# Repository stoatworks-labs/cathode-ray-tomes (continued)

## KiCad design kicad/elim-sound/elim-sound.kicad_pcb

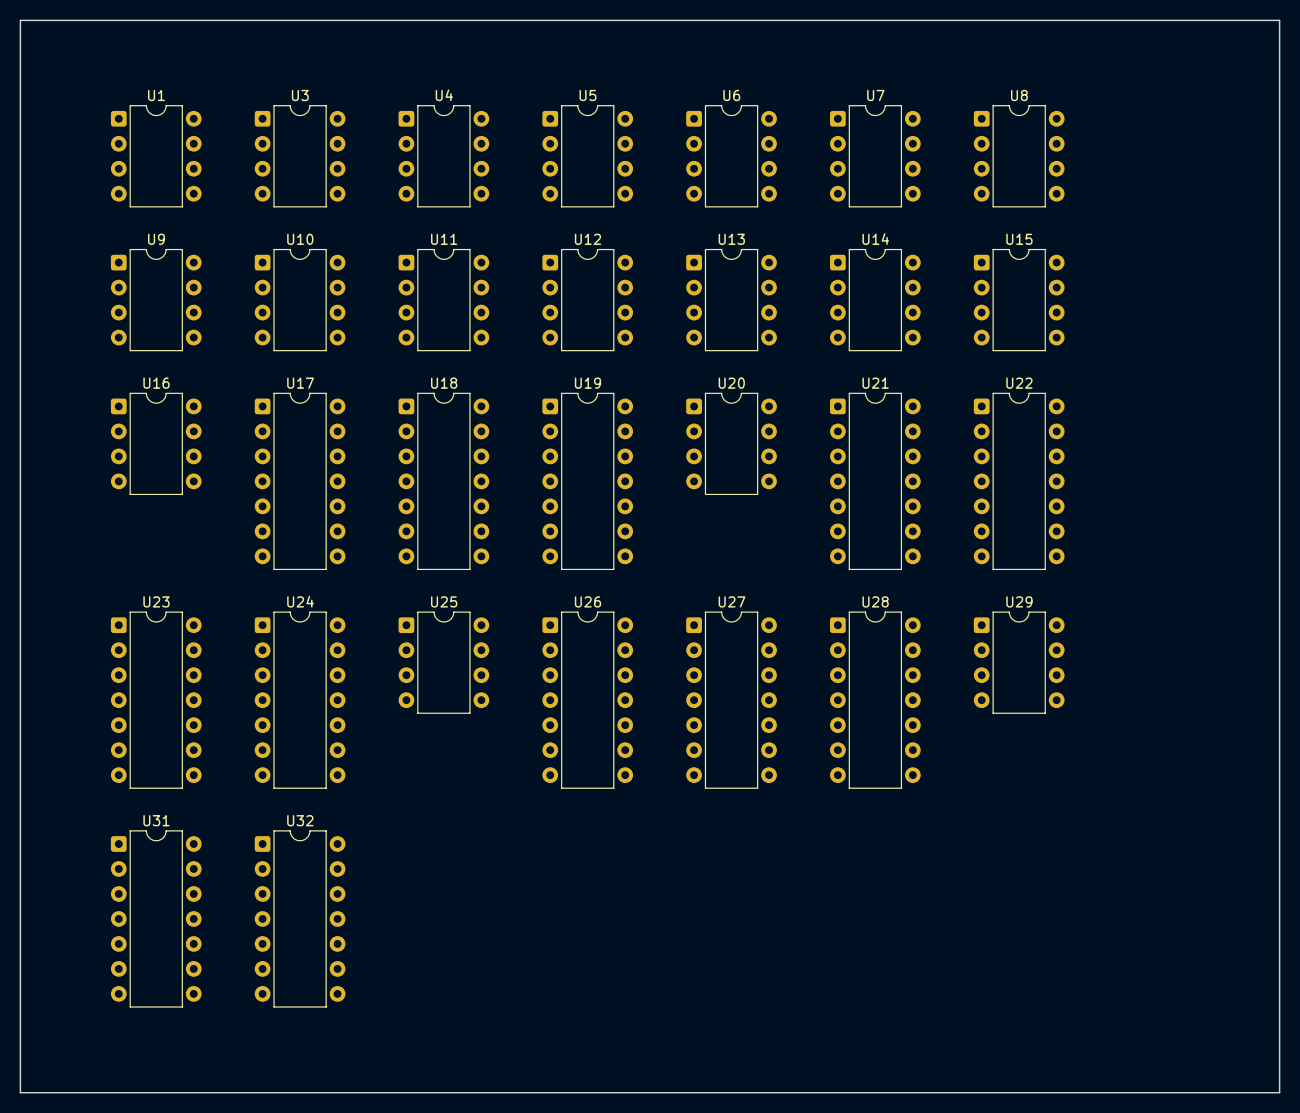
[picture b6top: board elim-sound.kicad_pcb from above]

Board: 2 copper layers, 128.0 x 109.0 mm, 30 parts (0 on the bottom side), 35 nets, no tracks yet.

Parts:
U1, U3, U12, U29: TL081; DIP-8_W7.62mm
U4: MM5837; DIP-8_W7.62mm
U5, U13: NE555; DIP-8_W7.62mm
U6, U7, U8, U9, U10, U11, U14, U15: CA3080; DIP-8_W7.62mm
U16, U20: TL082; DIP-8_W7.62mm
U17, U18, U19, U22: CD4011; DIP-14_W7.62mm
U21, U23: CD4024; DIP-14_W7.62mm
U24: 7406; DIP-14_W7.62mm
U25: LM566; DIP-8_W7.62mm
U26: 74LS00; DIP-14_W7.62mm
U27, U28: 7407; DIP-14_W7.62mm
U31, U32: CD4069; DIP-14_W7.62mm

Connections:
+5V: U24.14, U26.14, U27.14, U28.14
+12V: U1.7, U3.7, U4.4, U5.8, U6.7, U7.7, U8.7, U9.7, U10.7, U11.7, U12.7, U13.8, U14.7, U15.7, U16.8, U17.14, U18.14, U19.14, U20.8, U21.14, U22.14, U23.14, U29.7, U31.14, U32.14
-12V: U1.4, U3.4, U4.2, U6.4, U7.4, U8.4, U9.4, U10.4, U11.4, U12.4, U14.4, U15.4, U16.4, U20.4, U29.4
GND: U4.1, U5.1, U13.1, U16.5, U17.7, U18.7, U19.7, U21.7, U22.7, U23.7, U24.7, U25.1, U26.7, U27.7, U28.7, U29.3, U31.7, U32.7
I_BACKGROUND_LSB: U26.10, U27.1
I_BACKGROUND_MSB: U26.9, U27.3
unnamed: U5.2, U5.6
unnamed: U13.2, U13.6
unnamed: U21.2, U22.3
unnamed: U22.11, U23.2
unnamed: U16.1, U25.5
unnamed: U5.4, U24.8
unnamed: U22.10, U22.12, U22.13
unnamed: U22.1, U22.2, U22.4
unnamed: U13.4, U24.10
unnamed: U17.10, U17.12, U17.13
unnamed: U18.1, U18.2, U18.4
unnamed: U18.10, U18.12, U18.13
unnamed: U19.1, U19.2, U19.4
unnamed: U19.10, U19.12, U19.13
unnamed: U18.6, U28.12
unnamed: U17.8, U28.4
unnamed: U18.8, U28.6
unnamed: U19.8, U28.8
unnamed: U19.6, U28.10
unnamed: U22.6, U27.10
unnamed: U22.8, U27.8
unnamed: U32.11, U32.12
unnamed: U31.6, U31.9
unnamed: U31.2, U31.3
unnamed: U32.6, U32.9
unnamed: U32.2, U32.3
unnamed: U26.8, U27.5
SUM_VCA: U6.6, U7.6, U8.6, U9.6, U10.6, U11.6, U12.3, U14.6, U15.6
WBN: U3.2, U3.6

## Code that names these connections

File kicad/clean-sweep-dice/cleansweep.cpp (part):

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
  //page 1
#define _B999   VCC
#define _SCOR   "5G", 9
#define _5SCOA  "8G", 8
#define _5SCOB  "8G", 11
#define _5SCAA  "9J", 3
#define _SCA0   "8K", 14
#define _SCA1   "8K", 13
#define _SCA2   "8K", 12
#define _SCA3   "8K", 11
#define _5SCBB  "9J", 8
#define _SCB0   "7K", 14
#define _SCB1   "7K", 13
#define _SCB2   "7K", 12
#define _SCB3   "7K", 11
#define _5SCCC  "2J", 11
#define _SCC0   "6K", 14
#define _SCC1   "6K", 13
#define _SCC2   "6K", 12
#define _SCC3   "6K", 11
#define _5SBAA  "9J", 6
#define _SBA0   "8L", 14
#define _SBA1   "8L", 13
#define _SBA2   "8L", 12
#define _SBA3   "8L", 11
#define _5SBBB  "9J", 11
#define _SBB0   "7L", 14
#define _SBB1   "7L", 13
#define _SBB2   "7L", 12
#define _SBB3   "7L", 11
#define _5SBCC  "3L", 3
#define _SBC0   "6L", 14
#define _SBC1   "6L", 13
#define _SBC2   "6L", 12
#define _SBC3   "6L", 11

#define _5SCDA  "8J", 8
#define _5SCDB  "7H", 13
#define _SCDC   "9K", 4
#define _5SEDA  "9K", 13
#define _1SEDA  "9A", 12
#define _GANC   "7M", 9
#define _5GANC  "7M", 7
#define _5SBDA  "9L", 8
#define _5SBDB  "9K", 1
#define _SBDC   "9K", 10
#define _5SUBL  "0K", 6
#define _9XEFE  "SWREPLAYYN", 3  //vcc=no gnd=yes
#define _EFEE   "4M", 1

#define _NACM   "7J", 6
#define _NACL   "7J", 8
#define _5NABA  "1J", 6
#define _NBA0   "6J", 14
#define _NBA1   "6J", 13
#define _NBA2   "6J", 12
#define _NBA3   "6J", 11
#define _7ENDA  "8J", 6
#define _ENDB   "7H", 10
#define _9XBL5  "SWBALLS35", 3  //vcc=3 gnd=5 
#define _BL57   "1L", 13
#define _5BL57  "9A", 10
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#define _BL35   "4M", 10
#define _5BL35  "4M", 4

#define _NGTA   "2F", 3
#define _5NGTB  "3F", 1
#define _NGTC   "3F", 10
#define _5NGTC  "4B", 8  //number video gate
#define _5DNBA  "1G", 6
#define _DNBB   "3F", 4  //ball count gate
#define _ACLN   "2F", 11
#define _FNCA   "3H", 6
#define _FNCB   "3H", 8
#define _5GNCA  "2H", 3
#define _GNCB   "2F", 6
#define _5GNCC  "3F", 13
#define _5GBCA  "1G", 8
#define _GBCB   "2H", 11
#define _5GBCC  "0J", 6
#define _1GBCC  "4B", 6 //number gate
#define _5CNPA  "2H", 6  
#define _AERB   "2H", 8
#define _AERA   "0G", 3
#define _AERC   "2F", 8
#define _5AERD  "1H", 8 //left aerrow gate
#define _5AERE  "1H", 6 //right aerrow gate
#define _5CRBK  "0H", 6

#define _AFNA   "2G", 6
#define _AFNB   "2G", 8
#define _5AFNE  "0J", 8
#define _AFNC   "3G", 6
#define _AFND   "3G", 8
#define _5AFNF  "0J", 12
#define _AFNG   "1J", 8
#define _AFNH   "1J", 12
#define _5AGOT  "3J", 10
#define _AROT   "3J", 13 //aerrow output gate
#define _5SUBK  "2J", 3
#define _5ARBK  "2J", 6
#define _5ASBK  "2J", 8

#define _NCA0   "5K", 5
#define _NCA1   "5L", 5
#define _NCA2   "4K", 5
#define _NCA3   "4L", 5

#define _5NCA3  "4B", 12
#define _ILSB   "0G", 6
#define _5LODD  "0H", 8
#define _NLC3   "2L", 8
#define _NCG7   "3K", 9
#define _NCG6   "3K", 7
#define _NCG5   "3K", 6
#define _NCG4   "3K", 5
#define _NCG3   "3K", 4
#define _NCG2   "3K", 3
#define _NCH7   "0F", 8
#define _NCH6   "4F", 8
#define _5NCHA  "3L", 6
#define _5NCHB  "3L", 8
#define _5NCHC  "3L", 11
#define _NCIV   "2K", 13  //number video

  //page 2
#define _T999   VCC
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#define _1TQ05   "1B", 5
#define _6TQ05   "1A", 8
#define _2TQ05   "1A", 11
#define _THSC    "1B", 9
#define _5THSC   "1B", 7   //H sync
#define _6THSC   "1C", 3
#define _2THSC   "1C", 6
#define _TCSC    "4A", 11  //Composit Sync
#define _TEC0    "2A", 14
#define _TEC1    "2A", 13
#define _TEC2    "2A", 12
#define _TEC3    "2A", 11
#define _TECA    "2A", 15
#define _TEC4    "2B", 14
#define _TEC5    "2B", 13
#define _TEC6    "2B", 12
#define _TEC7    "2B", 11
#define _TECB    "2B", 15
#define _5TECC   "2C", 3
#define _1TECC   "0B", 10
#define _TEC8    "3A", 5
#define _5TEC8   "3A", 6
#define _5TECD   "2C", 6
#define _5TEG8   "2C", 8
#define _5TEG7   "2C", 11
#define _1TEG7   "0B", 12
#define _5TEC5   "4B", 2
#define _TL32    "0L", 11
#define _TLC0    "3B", 14
#define _TLC1    "3B", 13
#define _TLC2    "3B", 12
#define _TLC3    "3B", 11
#define _TLCA    "3B", 15
#define _TLC4    "3C", 14
#define _TLC5    "3C", 13
#define _TLC6    "3C", 12
#define _TLC7    "3C", 11
#define _TLCB    "3C", 15
#define _5TLCC   "4A", 3
#define _1TLCC   "4B", 4  //top and bottom border
#define _TLC8    "3A", 9  //top border
#define _5TLC8   "3A", 7
#define _5TLCD   "4A", 6
#define _5TLG8   "4A", 8
#define _TCSA    "4D", 6
#define _5TVSC   "4C", 8   //V sync
#define _5TEC2   "2D", 2
#define _5TEC3   "2D", 4
#define _5TEC4   "2D", 6
#define _1TEC4   "2D", 8
#define _1TEC5   "2D", 10
#define _5TEC6   "2D", 12
#define _5TEC7   "3D", 2
#define _5TEC1   "3D", 4
#define _5TEC0   "3D", 6
#define _5TLC1   "3D", 8
#define _5TLC2   "3D", 10
#define _1PGOT   "3D", 12

#define _TLNA    "1D", 8  
#define _TLHB    "1E", 8 
#define _TLNC    "0C", 5
#define _5TLNC   "0C", 6
#define _TLND    "0C", 9
#define _5TLND   "0C", 7
#define _TLNE    "2E", 11   //Horz Boundry
#define _THBL    "1D", 11   //Horz Blanking

#define _TLGV    "0L", 6
#define _5TVBL   "3J", 1
#define _COBL    "3J", 4
#define _5CVID   "0K", 3
#define _NCOT    "0L", 3
#define _5TLBG   "1L", 4   //dot vid
#define _VIDA    "9L", 6   //comp video output
#define _5TBCF   "1L", 1
#define _1TBCF   "8M", 12
#define _5ALVD   "1L", 10 
 
#define _WRTZ    "5A", 5
#define _WRTA    "5A", 9
#define _5WRTA   "5A", 7
#define _RESA    "4C", 3
#define _WRTB    "5D", 3
#define _5PONF   "4E", 1
#define _5PONG   "4E", 4
#define _PVID_P1 "5B", 6  //P1 dot output
#define _PVID_P2 "5C", 6  //P2 dot output
#define _PVID    "COMBINE", 4  //hack to combine P1 and P2 dot output
#define _1PVBL   "0K", 8
#define _5TLC4   "1F", 2
#define _5TLC5   "1F", 4
#define _5TLC6   "1F", 6
#define _5TLC7   "1F", 8
#define _5THBL   "1F", 10
#define _1RRLM   "1F", 12

#define _TE10    "2E", 3
#define _TL10    "2E", 6
#define _5CONR   "4C", 6
#define _PGHT    "2E", 8
#define _PVGT    "3E", 3
#define _PGTA    "1D", 3
#define _PHGU    "3E", 6
#define _PVGU    "3E", 8
#define _PGTB    "4E", 10
#define _PGTC    "1E", 6   //dot size and shape
#define _5PGOT   "0D", 8   //dot video shaped and blanked
#define _5PVBU   "0D", 6
#define _5PVBL   "0E", 6
#define _PERA    "0F", 6   //ball and dot intercept
#define _5RTEA   "4E", 13  //write "1" into memory

#define _TE78    "1D", 6
#define _5RRLA   "0E", 8
#define _5RRLB   "4C", 11
#define _5RRLM   "5D", 6
#define _RLAA    "7M", 5
#define _RLA0    "5E", 5
#define _5RLA0   "5E", 6
#define _RBLA    "6A", 15
#define _RLA1    "6A", 14
#define _RLA2    "6A", 13
#define _RLA3    "6A", 12
#define _RLA4    "6A", 11
#define _RBLB    "5E", 9 //pin not labeled on diagram
#define _RGTE    "7C", 3 //stop paddle generation once per horz line
#define _5TL01   "1C", 11
#define _RL34    "3E", 11
#define _TL01    "4D", 8
#define _5HITA   "6B", 6
#define _5RLA1   "0K", 11
#define _5RRST   "7A", 3
#define _5RRSU   "7A", 6
//#define _RPFA    "X7405", 2
#define _RPFA    "PADDLE", 2
#define _RAT7    "6C", 9
#define _RAT6    "6C", 7
#define _RAT5    "6C", 6
#define _RAT4    "6C", 5
#define _RAT3    "6C", 4
#define _RAT2    "6C", 3
#define _RAT1    "6C", 2
#define _RAT0    "6C", 1
#define _RVIA    "6D", 6
#define _5RVID   "6E", 6 //paddle video

  //Page 3
#define _N999    VCC
#define _5RHD1   "7B", 2
#define _RHD2    "7B", 5
#define _RHD3    "7B", 7
#define _5RHCL   "7B", 10
#define _RH12    "7A", 8
#define _RSP1    "7C", 6
#define _RSP2    "7C", 8
#define _RSP3    "7C", 11
#define _BPE3    "7D", 9
#define _BPE2    "7D", 7
#define _BPE1    "7D", 6
#define _BPE0    "7D", 5
#define _BPL3    "7D", 4
#define _BPL2    "7D", 3
#define _BPL1    "7D", 2
#define _BPL0    "7D", 1
#define _5ESCL   "6F", 1   // clear register for serve
#define _KBAL    "7G", 3   // ball and horz line intercept
#define _TL48    "5D", 8
#define _5TL48   "1C", 8
#define _RVIC    "7G", 6
#define _KBAR    "7G", 8   // ball and paddle intercept
#define _ENDD    "0G", 8
#define _5PHLB   "9D", 3
#define _5RLA4   "0G", 11
#define _5PHRC   "9F", 3
#define _5BSCL   "9E", 6   // ball control left and right
#define _5BSUP   "9E", 7   // ball control up and down
#define _TL49    "3M", 9
#define _5KBAS   "8G", 3   // ball and top intercept
#define _5UPEA   "9F", 6
#define _UPEB    "6F", 13
#define _5UPEC   "9F", 8
#define _5UPGA   "9F", 11
#define _5UPAA   "7G", 11

#define _5BELD   "7A", 11
#define _BECA    "7E", 15
#define _BECB    "7F", 9
#define _BEBB    "5D", 11
#define _BECC    "8F", 15
#define _5BVAA   "9B", 1
#define _BEGA    "8A", 2
#define _BEGB    "8A", 5
#define _BEGC    "8A", 7
#define _BEGD    "8A", 10
#define _BEGE    "8A", 12
#define _BEGF    "8A", 15
#define _BEGG    "8B", 2
#define _BEGH    "8B", 5
#define _1PERA   "8B", 7
#define _1KBAR   "8B", 10
#define _6TEG8   "8B", 12
#define _6CVID   "8B2", 15
#define _5BVAB   "9B", 4
#define _5BVAC   "9B", 10
#define _5BVAD   "9B", 13
#define _BVBA    "9C", 8
#define _BVCA    "9D", 6
#define _BVCB    "9D", 8
#define _BVCD    "9D", 11
#define _BLCA    "8D", 15
#define _BLCB    "8E", 15
#define _5BLCB   "9A", 4
#define _5BLGA   "8C", 2
#define _5BLGB   "8C", 5
#define _5BLGC   "8C", 7
#define _5BLGD   "8C", 10
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
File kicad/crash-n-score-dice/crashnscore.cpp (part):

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/* sheet 1 */

#define _CLOCK       "A1", 2
#define _CLOCKn      "A1", 4
#define _1H          "A2", 14
#define _4H          "A2", 12
#define _8H          "A2", 11
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#define _128H        "C2", 11
#define _256H        "B2", 14
#define _512H        "B2", 13
#define _HRESETn     "A3", 8
#define _VRESETn     "B3", 5
#define _VRESET      "B3", 6
#define _VSYNC       "F1", 10
#define _VSYNCn      "F1", 13
#define _1V          "E1", 12
#define _2V          "E1", 9
#define _4V          "E1", 8
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#define _128V        "D1", 11
#define _256V        "FH1", 3
#define _256Vn       "FH1", 2
#define _VCLOCKn     "C4", 8
#define _128Vn       "A1", 8  //wrong on diagram
#define _32Hn        "J3", 4
#define _1Hn         "J3", 2
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#define _256Hn       "C3", 4
#define _8Vn         "A1", 6
#define _64Vn        "C3", 6
#define _HSYNC       "B3", 8
#define _OBJ0        "D2", 12
#define _OBJ1        "D2", 11
#define _OBJ2        "D2", 10
#define _OBJ3        "D2", 9
#define _SHAPES      "K3", 9
#define _FLAGSn      "H3", 6
#define _FLAGS       "J3", 8
#define _BARRIORSn   "H3", 11
#define _SLICKSn     "H3", 3
#define _CARIPLUSSLICKS "J4", 11
#define _CARIIPLUSSLICKS "J4", 3
#define _BARRIERVIDEO "R3", 12
#define _BBFI        "F4", 13
#define _BBFII       "F4", 10

#define _SCOREWINDOW "F1", 1
#define _WHITESCORE  "H2", 4
#define _BLACKSCOREn "H3", 8

#define _HIT1        "H4", 6
#define _HIT1n       "H4", 7
#define _HIT2        "H4", 10
#define _HIT2n       "H4", 9
#define _HIT         "D4", 6
#define _SCORETONE   "F3", 8
#define _SA          "E4", 3
#define _SB          "E4", 6
#define _WHITEFLAG   "C3", 2
#define _BLACKFLAGS  "N4", 13
#define _BLACKFLAGSn "R3", 10
#define _FC          "C1", 3
#define _CARRESETI   "M4", 5
#define _CARRESET2   "N4", 10

/* sheet 2 */

#define _COIN        "P3", 8
#define _COIN1n      "A7", 9
#define _1CRSTARTn   "K4", 8
#define _2CRSTARTn   "K4", 6
#define _2PLAYERn    "M4", 9
#define _2PLAYER     "M4", 8
#define _STARTn      "C10", 4
#define _START       "K5", 3
#define _ATTRACTn    "J7", 5
#define _ATTRACT     "J7", 6
#define _ATTRACTI    "C10", 12
#define _GT1         "P10", 9
#define _GT2         "P10", 8
#define _ENDGAME     "P10", 11
#define _ENDGAMEn    "N10", 10
#define _FLASHn      "F10", 8
#define _2CREDITn    "N4",4
#define _2CREDIT     "R3", 2
#define _1OR2CREDIT  "P3", 3
#define _1OR2CREDITn "R3", 6
#define _Qn          "LATCH", 3
#define _Q           "E10", 10
#define _BG1n        "N1", 5
#define _BG2n        "N1", 9
#define _BONUSCOIN   "P3", 6
#define _FREEGAMETONE "MN1", 6

/* sheet 3 */

#define _R0I         "F8", 6  //R for rotation
#define _R1I         "F8", 7
#define _R2I         "H8", 3
#define _R3I         "H8", 2
#define _R4I         "H8", 6
#define _D1I         "H7", 16 //D for direction (latched rotation)
#define _D2I         "H7", 15
#define _D3I         "H7", 10
#define _D4I         "H7", 9
#define _1FI         "D8", 12 //F for frame
#define _2FI         "D8", 9
#define _4FI         "D8", 8
#define _8FI         "D8", 11
#define _16FIn       "C7", 6
#define _SPEED1I     "E9", 3
#define _SPEED2I     "E9", 2
#define _SPEED3I     "E9", 6
#define _SPEED4I     "E9", 7
#define _SPEED5I     "C7", 3
#define _SPEED5In    "C7", 2
#define _STOPI       "C9", 6
#define _GOI         "D9", 5
#define _SKIDI       "B7", 3
#define _SKIDIn      "D7", 10
#define _CRASHSEQIn  "A5", 9
#define _CRASHIn     "B5", 8

#define _CLOCKI      "A6", 8
#define _VRESETIn    "A6", 10
#define _C0I         "E5", 14 //C for column
#define _C1I         "E5", 13
#define _C2I         "E5", 12
#define _C3I         "E5", 11
#define _C4I         "D5", 14
#define _L0I         "D6", 13 //L for line
#define _L1I         "D6", 12
#define _L2I         "D6", 11
#define _CARRESETIn  "A6", 2
#define _128CVI      "F5", 5
#define _VTCIn       "B6", 6 //Vertical Terminal Count
#define _VTCI        "A6", 6
#define _CARWINDOWIn "B6", 8
#define _CARI        "F5", 3
#define _CARIn       "F5", 2
#define _MFI         "D10", 3

/* sheet 4 */

#define _R0II        "P8", 6
#define _R1II        "P8", 7
#define _R2II        "R8", 3
#define _R3II        "R8", 2
#define _R4II        "R8", 6
#define _D1II        "R7", 16
#define _D2II        "R7", 15
#define _D3II        "R7", 10
#define _D4II        "R7", 9
#define _1FII        "M8", 12
#define _2FII        "M8", 9
#define _4FII        "M8", 8
#define _8FII        "M8", 11
#define _16FIIn      "L7", 6
#define _SPEED1II    "N9", 3
#define _SPEED2II    "N9", 2
#define _SPEED3II    "N9", 6
#define _SPEED4II    "N9", 7
#define _SPEED5II    "L7", 3
#define _SPEED5IIn   "L7", 2
#define _STOPII      "L9", 6
#define _GOII        "M9", 5
#define _SKIDII      "K7", 3
#define _SKIDIIn     "M7", 10
#define _CRASHSEQIIn "J5", 9
#define _CRASHIIn    "K5", 8
#define _CLOCKII     "J6", 8
#define _VRESETIIn   "J6", 10
#define _C0II        "N5", 14
#define _C1II        "N5", 13
#define _C2II        "N5", 12
#define _C3II        "N5", 11
#define _C4II        "M5", 14
#define _L0II        "M6", 13
#define _L1II        "M6", 12
#define _L2II        "M6", 11
#define _CARRESETIIn "J6", 2
#define _128CVII     "P5", 5
#define _VTCIIn      "K6", 6
#define _VTCII       "J6", 6
#define _CARWINDOWIIn "K6", 8
#define _CARII       "P5", 3
#define _CARIIn      "P5", 2


//*****circuit layout  *****
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CONNECTION(VCC,              "FH1", 1)
CONNECTION(_128V,            "FH1", 12)
CONNECTION(VCC,              "FH1", 4)
CONNECTION(_VRESETn,         "FH1", 13)  //pin number missing on diagram

CONNECTION(_VSYNCn,          "C4", 13)
CONNECTION(_HSYNC,           "C4", 12)
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
/* video (sheet1, right, middle) */

CONNECTION("VIDEO", Video::VBLANK_PIN, _VSYNC)
CONNECTION("VIDEO", Video::HBLANK_PIN, _HSYNC)

CONNECTION(_CARIIn,          "C4", 1)
CONNECTION(_BLACKSCOREn,     "C4", 2)
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CONNECTION("P2", 12,       "P3", 9) 
CONNECTION(VCC,            "P3", 10)  // skip coin 2

// skipping coin 2 circuit



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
